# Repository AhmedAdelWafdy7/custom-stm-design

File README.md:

# Custom STM Design

This is a README file for the custom-stm-design PCB board, a versatile and powerful board that features the STM32F405 MCU. This board can handle a wide range of applications, thanks to its rich set of peripherals and interfaces. 

The board supports power supply from +12V, using a buck converter to regulate the voltage for the MCU and other components. It also supports USB power and data, allowing you to connect the board to your computer or other devices. You can use the USB interface to program, debug, or communicate with the board.

The board also provides UART and I2C interfaces, which are useful for serial communication with sensors, actuators, or other boards. You can use these interfaces to expand the functionality of your board or integrate it with other systems.

Finally, the board supports SWD debugging, which is a low-pin-count interface that allows you to access the core features of the MCU. You can use SWD debugging to monitor, control, or modify the behavior of your board in real time.

The custom-stm-design PCB board is a great choice for anyone who wants to explore the capabilities of the STM32F405 MCU or create their own projects using this powerful and flexible platform. You can find more information about the board specifications, schematics, and firmware in the following sections.

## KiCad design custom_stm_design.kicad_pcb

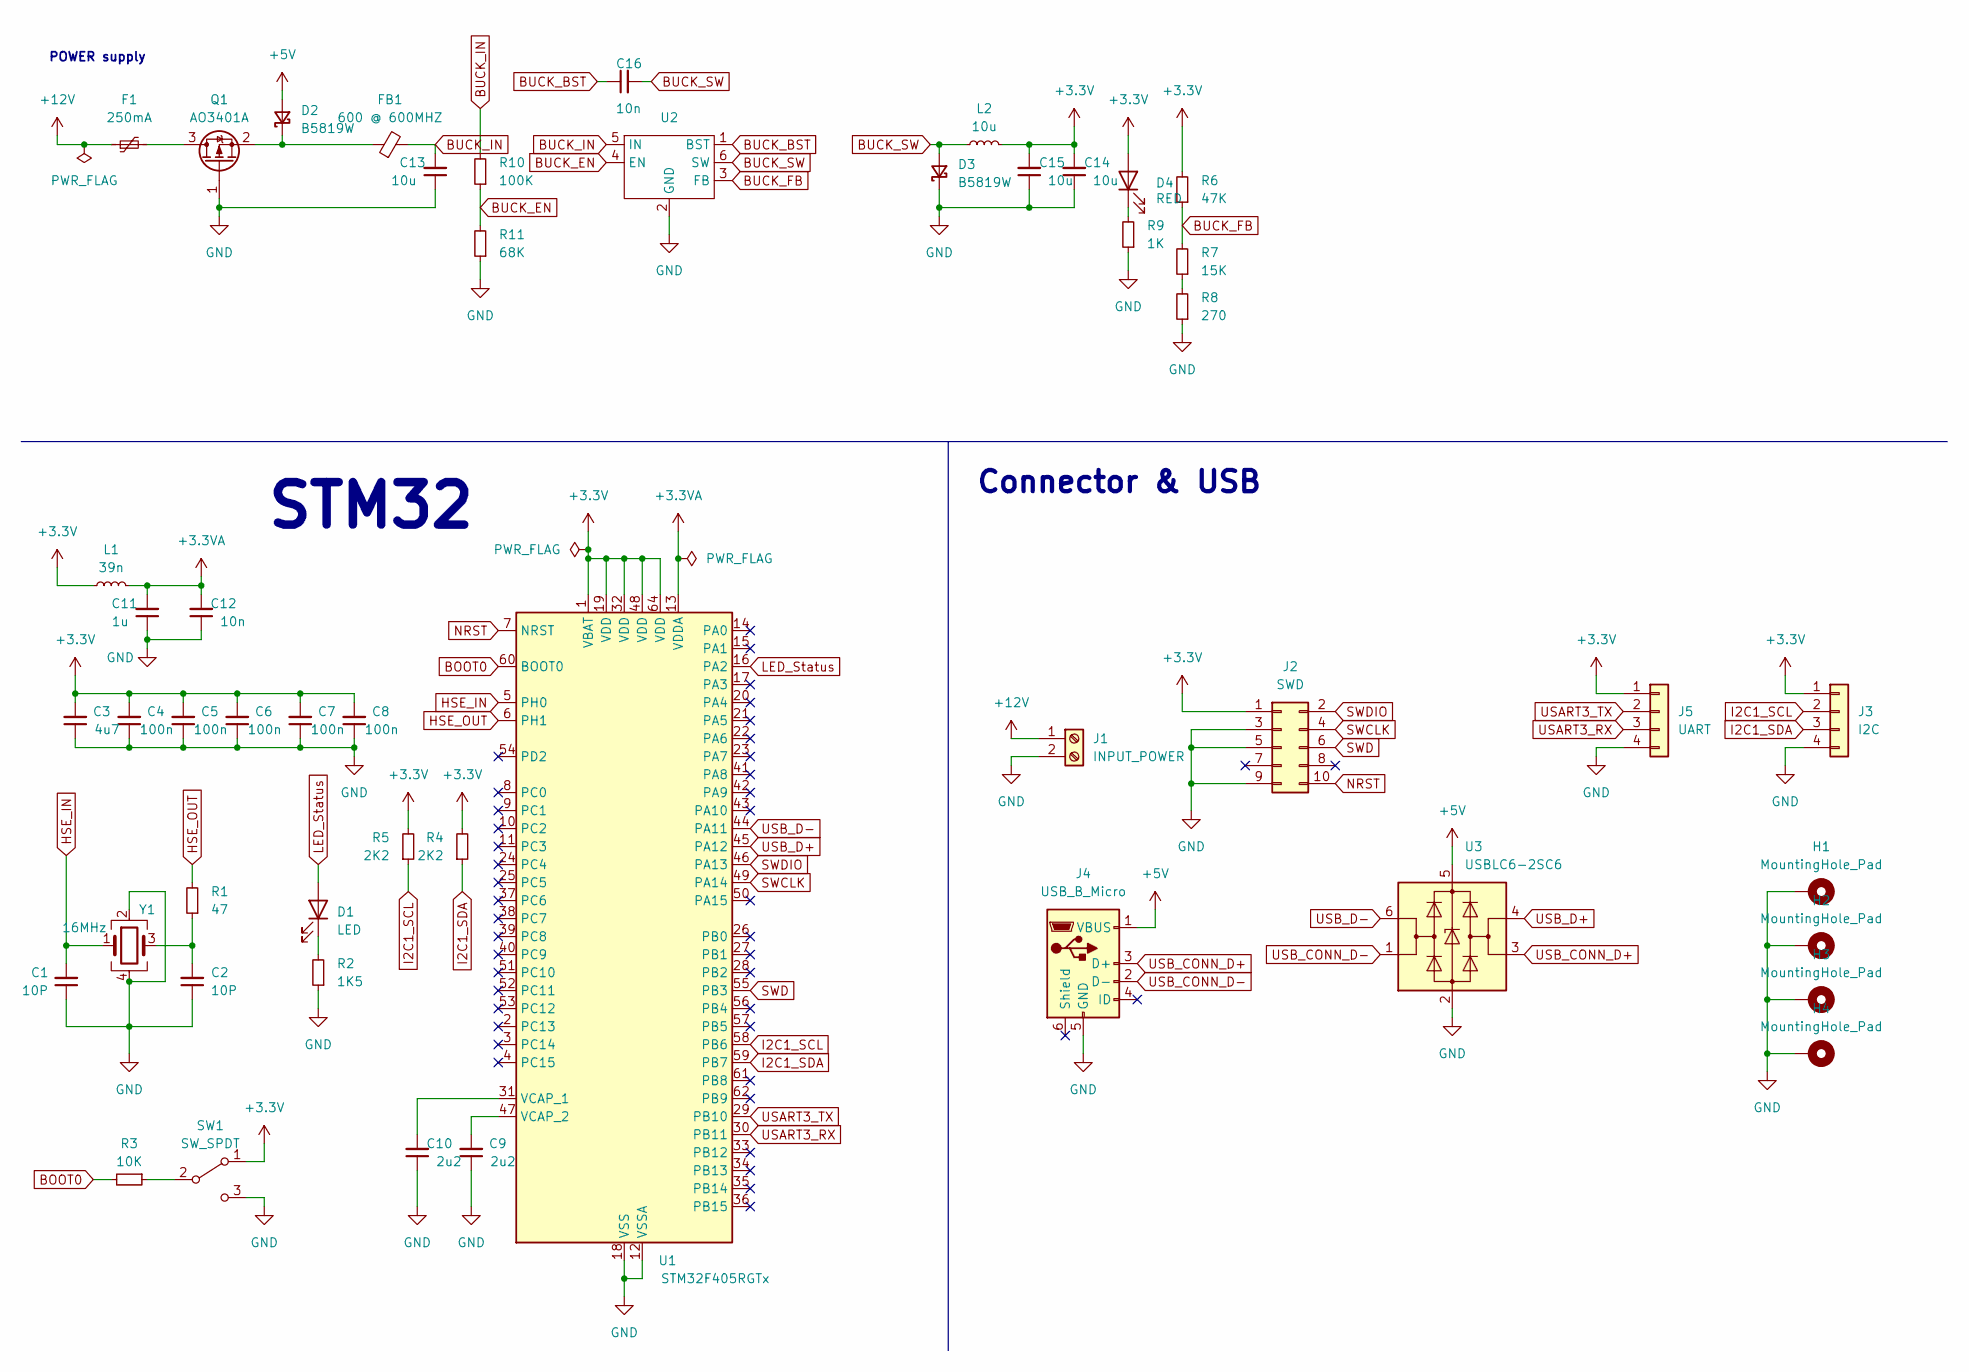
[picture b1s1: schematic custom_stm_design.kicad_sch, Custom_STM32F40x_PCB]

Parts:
C1, C2: 10P; C_0402_1005Metric
C3: 4u7; C_0603_1608Metric
C4, C5, C6, C7, C8: 100n; C_0402_1005Metric
C9, C10: 2u2; C_0603_1608Metric
C11: 1u; C_0603_1608Metric
C12: 10n; C_0603_1608Metric
C13, C14, C15: 10u; C_1206_3216Metric
C16: 10n; C_0402_1005Metric
D1: LED; LED_0603_1608Metric
D2, D3: B5819W; D_SOD-123
D4: RED; LED_0603_1608Metric
F1: 250mA; Fuse_1206_3216Metric
FB1: 600 @ 600MHZ; L_0805_2012Metric
H1, H2, H3, H4: MountingHole_Pad; MountingHole_4.3mm_M4_Pad_Via
J1: INPUT_POWER; TerminalBlock_Phoenix_PT-1,5-2-3.5-H_1x02_P3.50mm_Horizontal
J2: SWD; PinHeader_2x05_P1.27mm_Vertical_SMD
J3: I2C; Molex_PicoBlade_53048-0410_1x04_P1.25mm_Horizontal
J4: USB_B_Micro; USB_Mini-B_Lumberg_2486_01_Horizontal
J5: UART; Molex_PicoBlade_53048-0410_1x04_P1.25mm_Horizontal
L1: 39n; L_0402_1005Metric
L2: 10u; L_Sunlord_MWSA0518S
Q1: AO3401A; SOT-23
R1: 47; R_0402_1005Metric
R2: 1K5; R_0603_1608Metric
R3: 10K; R_0603_1608Metric
R4, R5: 2K2; R_0402_1005Metric
R6: 47K; R_0603_1608Metric
R7: 15K; R_0603_1608Metric
R8: 270; R_0603_1608Metric
R9: 1K; R_0603_1608Metric
R10: 100K; R_0603_1608Metric
R11: 68K; R_0603_1608Metric
SW1: SW_SPDT; SW_SPDT_PCM12
U1: STM32F405RGTx; LQFP-64_10x10mm_P0.5mm
U2: SOT-23-6
U3: USBLC6-2SC6; SOT-23-6
Y1: 16MHz; Crystal_SMD_3225-4Pin_3.2x2.5mm

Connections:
+3.3V: C3.2, C4.2, C5.2, C6.2, C7.2, C8.2, C14.2, C15.2, D4.2 (A), J2.1, J3.1, J5.1, L1.1, L2.2, R4.2, R5.2, R6.2, SW1.1 (A), U1.1 (VBAT), U1.19 (VDD), U1.32 (VDD), U1.48 (VDD), U1.64 (VDD)
+3.3VA: C11.2, C12.2, L1.2, U1.13 (VDDA)
+5V: D2.2 (A), J4.1 (VBUS), U3.5 (VBUS)
+12V: F1.1, J1.1
BOOT0: R3.2, U1.60 (BOOT0)
BUCK_BST: C16.1, U2.1 (BST)
BUCK_EN: R10.1, R11.2, U2.4 (EN)
BUCK_FB: R6.1, R7.2, U2.3 (FB)
BUCK_IN: C13.2, FB1.2, R10.2, U2.5 (IN)
BUCK_SW: C16.2, D3.2 (A), L2.1, U2.6 (SW)
GND: C1.1, C2.1, C3.1, C4.1, C5.1, C6.1, C7.1, C8.1, C9.1, C10.1, C11.1, C12.1, C13.1, C14.1, C15.1, D3.1 (K), H1.1, H2.1, H3.1, H4.1, J1.2, J2.3, J2.5, J2.9, J3.4, J4.5 (GND), J5.4, Q1.1 (G), R2.1, R8.1, R9.1, R11.1, SW1.3 (C), U1.12 (VSSA), U1.18 (VSS), U1.63 (VSS), U2.2 (GND), U3.2 (GND), Y1.2, Y1.4
HSE_IN: C1.2, U1.5 (PH0), Y1.1
HSE_OUT: R1.2, U1.6 (PH1)
I2C1_SCL: J3.2, R5.1, U1.58 (PB6)
I2C1_SDA: J3.3, R4.1, U1.59 (PB7)
LED_Status: D1.2 (A), U1.16 (PA2)
NRST: J2.10, U1.7 (NRST)
unnamed: C2.2, R1.1, Y1.3
unnamed: D1.1 (K), R2.2
unnamed: D2.1 (K), FB1.1, Q1.2 (S)
unnamed: D4.1 (K), R9.2
unnamed: F1.2, Q1.3 (D)
unnamed: R7.1, R8.2
unnamed: R3.1, SW1.2 (B)
unnamed: C10.2, U1.31 (VCAP_1)
unnamed: C9.2, U1.47 (VCAP_2)
SWCLK: J2.4, U1.49 (PA14)
SWD: J2.6, U1.55 (PB3)
SWDIO: J2.2, U1.46 (PA13)
USART3_RX: J5.3, U1.30 (PB11)
USART3_TX: J5.2, U1.29 (PB10)
USB_CONN_D+: J4.3 (D+), U3.3 (I/O2)
USB_CONN_D-: J4.2 (D-), U3.1 (I/O1)
USB_D+: U1.45 (PA12), U3.4 (I/O2)
USB_D-: U1.44 (PA11), U3.6 (I/O1)

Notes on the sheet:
POWER supply
Connector & USB
STM32

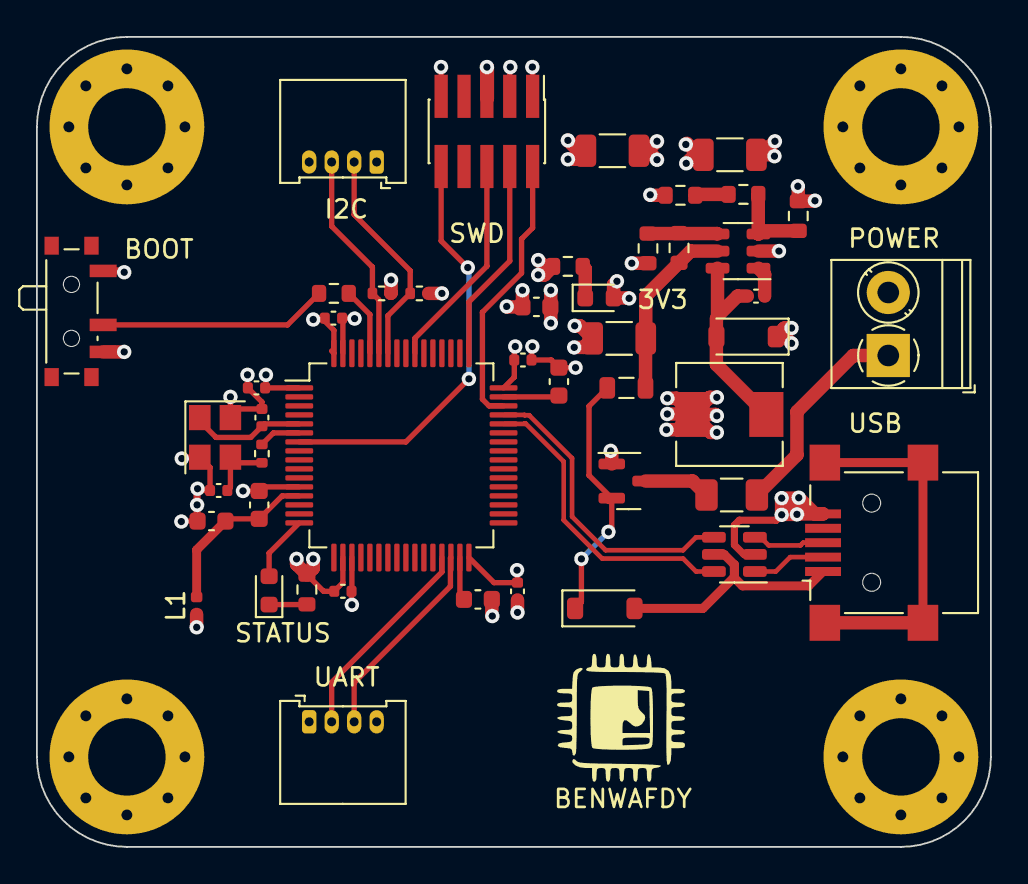
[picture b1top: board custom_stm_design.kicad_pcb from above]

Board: 4 copper layers, 53.0 x 45.0 mm, 50 parts (0 on the bottom side), 35 nets.

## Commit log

2023-10-17 add project files
